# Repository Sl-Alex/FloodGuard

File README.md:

# General description
Autonomous flood protection system, which can work for months from a single 18650 Li-ion battery.
Includes a battery charger as well as a HW monitoring circuit. Includes power MOSFET for external valve control circuit. Even if SW is stuck or microcontroller is dead you will hear beeping informing you that something is wrong.
Two protected guard inputs make a redundant and reliable system.

# Hardware
Both schematic and PCB were created with KiCAD. KiCAD project is located in the PCB subfolder. Project uses components from my [KiCAD_libs](https://github.com/Sl-Alex/KiCAD_libs) repository.<br />

# Software
Project is created in [EmBitz](https://www.embitz.org/). Project skeleton is created in STM32CubeMX.<br />

# Licensing
The whole project is available under GPL v3 license (see [LICENSE](LICENSE) file), except of files, which clearly mention other license type in the file header.

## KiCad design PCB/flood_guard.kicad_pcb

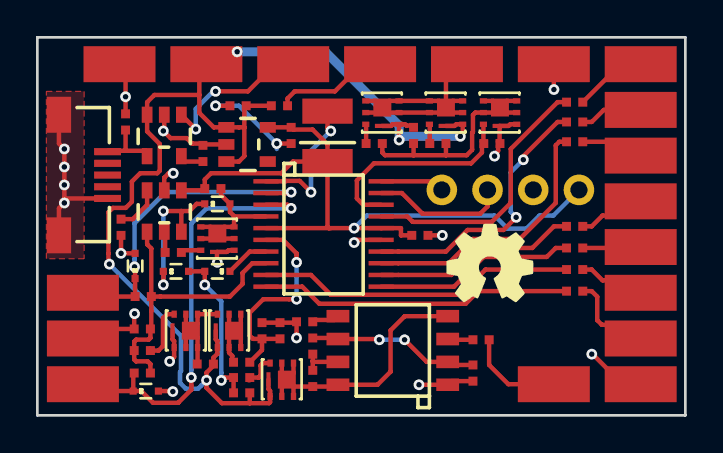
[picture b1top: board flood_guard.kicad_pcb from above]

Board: 2 copper layers, 36.0 x 21.0 mm, 77 parts (0 on the bottom side), 49 nets.

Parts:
C1, C2, C3, C4, C5, C7, C8: capacitor; 0402_C
C6: capacitor_el; case_B
D1, D2, D3: diode; SOD523
D4, D5: zener; SOD523
LG?1: LOGO; OSHW
R1, R2, R3, R4, R5, R6, R7, R8, R9, R10, R11, R12, R13, R14, R15, R16, R17, R18, R19, R20, R21, R22, R23, R24, R25, R26, R27, R28: resistor; 0402_R
U1: TPL5010; SOT23-6
U2: NCP551; SOT23-5
U3: TS555CN; SO8
U4: STC4054; SOT23-5
U5: STM32F030F4P6; TSSOP20
VT1, VT2, VT3: MOSFET_N_DGS; PQFN2x2
VT4, VT6, VT7, VT8: MOSFET_P_DGS; PQFN2x2
X1: USB2_MICRO_B_F1
X2: BUZZER+; PLS1_SMD
X4: BAT+; PLS1_SMD
X5: BAT-; PLS1_SMD
X6: CHG_LED-; PLS1_SMD
X7: CHG_LED+; PLS1_SMD
X8: 3V3; PLS1
X9: GND; PLS1
X10: SWCLK; PLS1
X11: SWDIO; PLS1
X12: VOUT; PLS1_SMD
X13, X16, X25: GND; PLS1_SMD
X14: GUARD0; PLS1_SMD
X15: GUARD1; PLS1_SMD
X18: LED0; PLS1_SMD
X19: LED1; PLS1_SMD
X20: LED2; PLS1_SMD
X21: LED3; PLS1_SMD
X22: LED4; PLS1_SMD
X23: LED5; PLS1_SMD
X24: LED6; PLS1_SMD

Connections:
3V3: C5.2, C6.1, C7.2, R8.2, U1.1, U2.5, U5.5, U5.16, X8.1
/BUZZER_PWR: R2.2, U3.4, U3.8, VT4.1
/BUZ_EN: D2.2, U5.7
/GUARD0: D4.2, R17.2, U5.2, X14.1
/GUARD1: D5.2, R18.2, U5.3, X15.1
/LED0: R21.1, U5.10
/LED1: R22.1, U5.9
/LED2: R23.1, U5.11
/LED3: R24.1, U5.12
/LED4: R25.1, U5.13
/LED5: R26.1, U5.14
/LED6: R27.1, U5.17
/LOAD: R13.2, U5.18, VT3.2
/MEAS: R11.1, R12.1, R17.1, R18.1, U1.4, U5.8
/SWCLK: U5.20, X10.1
/SWDIO: U5.19, X11.1
/VADC: C8.1, R19.1, R20.2, U5.6
/VBAT: C4.2, R7.1, R9.2, R14.2, R28.1, U2.1, U2.3, U4.3, VT4.3, VT6.3, VT7.3, VT8.3, X4.1
/VOUT: VT6.1, VT8.1, X12.1
/WAKE: R6.1, U1.5
/~CPU_RST: D1.1, R8.1, U5.4, VT1.1
/~RST: D1.2, D3.2, U1.6
GND: C1.1, C2.1, C3.1, C4.1, C5.1, C6.2, C7.1, C8.2, D4.1, D5.1, R1.1, R4.1, R11.2, R13.1, R19.2, U1.2, U2.2, U3.1, U4.2, U5.1, U5.15, VT1.3, VT2.3, VT3.3, X1.5, X1.6, X1.7, X5.1, X9.1, X13.1, X16.1, X25.1
unnamed: C1.2, R3.1, U3.2, U3.6
unnamed: C2.2, U3.5
unnamed: C3.2, U4.4, X1.1
unnamed: D2.1, D3.1, R9.1, R10.1
unnamed: R1.2, U1.3
unnamed: R2.1, R3.2, U3.7
unnamed: R4.2, U4.5
unnamed: R5.1, U3.3
unnamed: R5.2, X2.1
unnamed: R6.2, VT1.2
unnamed: R7.2, X7.1
unnamed: R10.2, VT4.2
unnamed: R12.2, VT2.2
unnamed: R14.1, VT2.1, VT7.2
unnamed: R15.1, VT6.2
unnamed: R15.2, R16.2, R28.2, VT3.1
unnamed: R16.1, VT8.2
unnamed: R20.1, VT7.1
unnamed: R21.2, X18.1
unnamed: R22.2, X19.1
unnamed: R23.2, X20.1
unnamed: R24.2, X21.1
unnamed: R25.2, X22.1
unnamed: R26.2, X23.1
unnamed: R27.2, X24.1
unnamed: U4.1, X6.1

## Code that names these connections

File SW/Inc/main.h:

/**
  ******************************************************************************
  * @file           : main.h
  * @brief          : Header for main.c file.
  *                   This file contains the common defines of the application.
  ******************************************************************************
  ** This notice applies to any and all portions of this file
  * that are not between comment pairs USER CODE BEGIN and
  * USER CODE END. Other portions of this file, whether 
  * inserted by the user or by software development tools
  * are owned by their respective copyright owners.
  *
  * COPYRIGHT(c) 2018 STMicroelectronics
  *
  * Redistribution and use in source and binary forms, with or without modification,
  * are permitted provided that the following conditions are met:
  *   1. Redistributions of source code must retain the above copyright notice,
  *      this list of conditions and the following disclaimer.
  *   2. Redistributions in binary form must reproduce the above copyright notice,
  *      this list of conditions and the following disclaimer in the documentation
  *      and/or other materials provided with the distribution.
  *   3. Neither the name of STMicroelectronics nor the names of its contributors
  *      may be used to endorse or promote products derived from this software
  *      without specific prior written permission.
  *
  * THIS SOFTWARE IS PROVIDED BY THE COPYRIGHT HOLDERS AND CONTRIBUTORS "AS IS"
  * AND ANY EXPRESS OR IMPLIED WARRANTIES, INCLUDING, BUT NOT LIMITED TO, THE
  * IMPLIED WARRANTIES OF MERCHANTABILITY AND FITNESS FOR A PARTICULAR PURPOSE ARE
  * DISCLAIMED. IN NO EVENT SHALL THE COPYRIGHT HOLDER OR CONTRIBUTORS BE LIABLE
  * FOR ANY DIRECT, INDIRECT, INCIDENTAL, SPECIAL, EXEMPLARY, OR CONSEQUENTIAL
  * DAMAGES (INCLUDING, BUT NOT LIMITED TO, PROCUREMENT OF SUBSTITUTE GOODS OR
  * SERVICES; LOSS OF USE, DATA, OR PROFITS; OR BUSINESS INTERRUPTION) HOWEVER
  * CAUSED AND ON ANY THEORY OF LIABILITY, WHETHER IN CONTRACT, STRICT LIABILITY,
  * OR TORT (INCLUDING NEGLIGENCE OR OTHERWISE) ARISING IN ANY WAY OUT OF THE USE
  * OF THIS SOFTWARE, EVEN IF ADVISED OF THE POSSIBILITY OF SUCH DAMAGE.
  *
  ******************************************************************************
  */

/* Define to prevent recursive inclusion -------------------------------------*/
#ifndef __MAIN_H__
#define __MAIN_H__

/* Includes ------------------------------------------------------------------*/

/* USER CODE BEGIN Includes */

/* USER CODE END Includes */

/* Private define ------------------------------------------------------------*/

#define GUARD0_Pin GPIO_PIN_0
#define GUARD0_GPIO_Port GPIOF
#define GUARD1_Pin GPIO_PIN_1
#define GUARD1_GPIO_Port GPIOF
#define VADC_Pin GPIO_PIN_0
#define VADC_GPIO_Port GPIOA
#define BUZ_EN_Pin GPIO_PIN_1
#define BUZ_EN_GPIO_Port GPIOA
#define MEAS_Pin GPIO_PIN_2
#define MEAS_GPIO_Port GPIOA
#define LED1_Pin GPIO_PIN_3
#define LED1_GPIO_Port GPIOA
#define LED0_Pin GPIO_PIN_4
#define LED0_GPIO_Port GPIOA
#define LED2_Pin GPIO_PIN_5
#define LED2_GPIO_Port GPIOA
#define LED3_Pin GPIO_PIN_6
#define LED3_GPIO_Port GPIOA
#define LED4_Pin GPIO_PIN_7
#define LED4_GPIO_Port GPIOA
#define LED5_Pin GPIO_PIN_1
#define LED5_GPIO_Port GPIOB
#define LED6_Pin GPIO_PIN_9
#define LED6_GPIO_Port GPIOA
#define LOAD_Pin GPIO_PIN_10
#define LOAD_GPIO_Port GPIOA

/* ########################## Assert Selection ############################## */
/**
  * @brief Uncomment the line below to expanse the "assert_param" macro in the 
  *        HAL drivers code
  */
/* #define USE_FULL_ASSERT    1U */

/* USER CODE BEGIN Private defines */

/* USER CODE END Private defines */

#ifdef __cplusplus
 extern "C" {
#endif
void _Error_Handler(char *, int);

#define Error_Handler() _Error_Handler(__FILE__, __LINE__)
#ifdef __cplusplus
}
#endif

#endif /* __MAIN_H__ */

/************************ (C) COPYRIGHT STMicroelectronics *****END OF FILE****/

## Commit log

2018-07-11 First version, it works, but can be improved further.
2018-07-11 README update
2018-08-19 Schematic update (correct pull-up resistors). Load "ON" time is limited to two cycles.
